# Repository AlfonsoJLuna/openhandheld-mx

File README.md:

# OpenHandheld MX

Open-source development board in the shape of a handheld game console.

 | 
:---: | :---:
Front | Back

## Related repositories

Example code for this board can be found in [openhandheld-mx-sdk](https://github.com/AlfonsoJLuna/openhandheld-mx-sdk).

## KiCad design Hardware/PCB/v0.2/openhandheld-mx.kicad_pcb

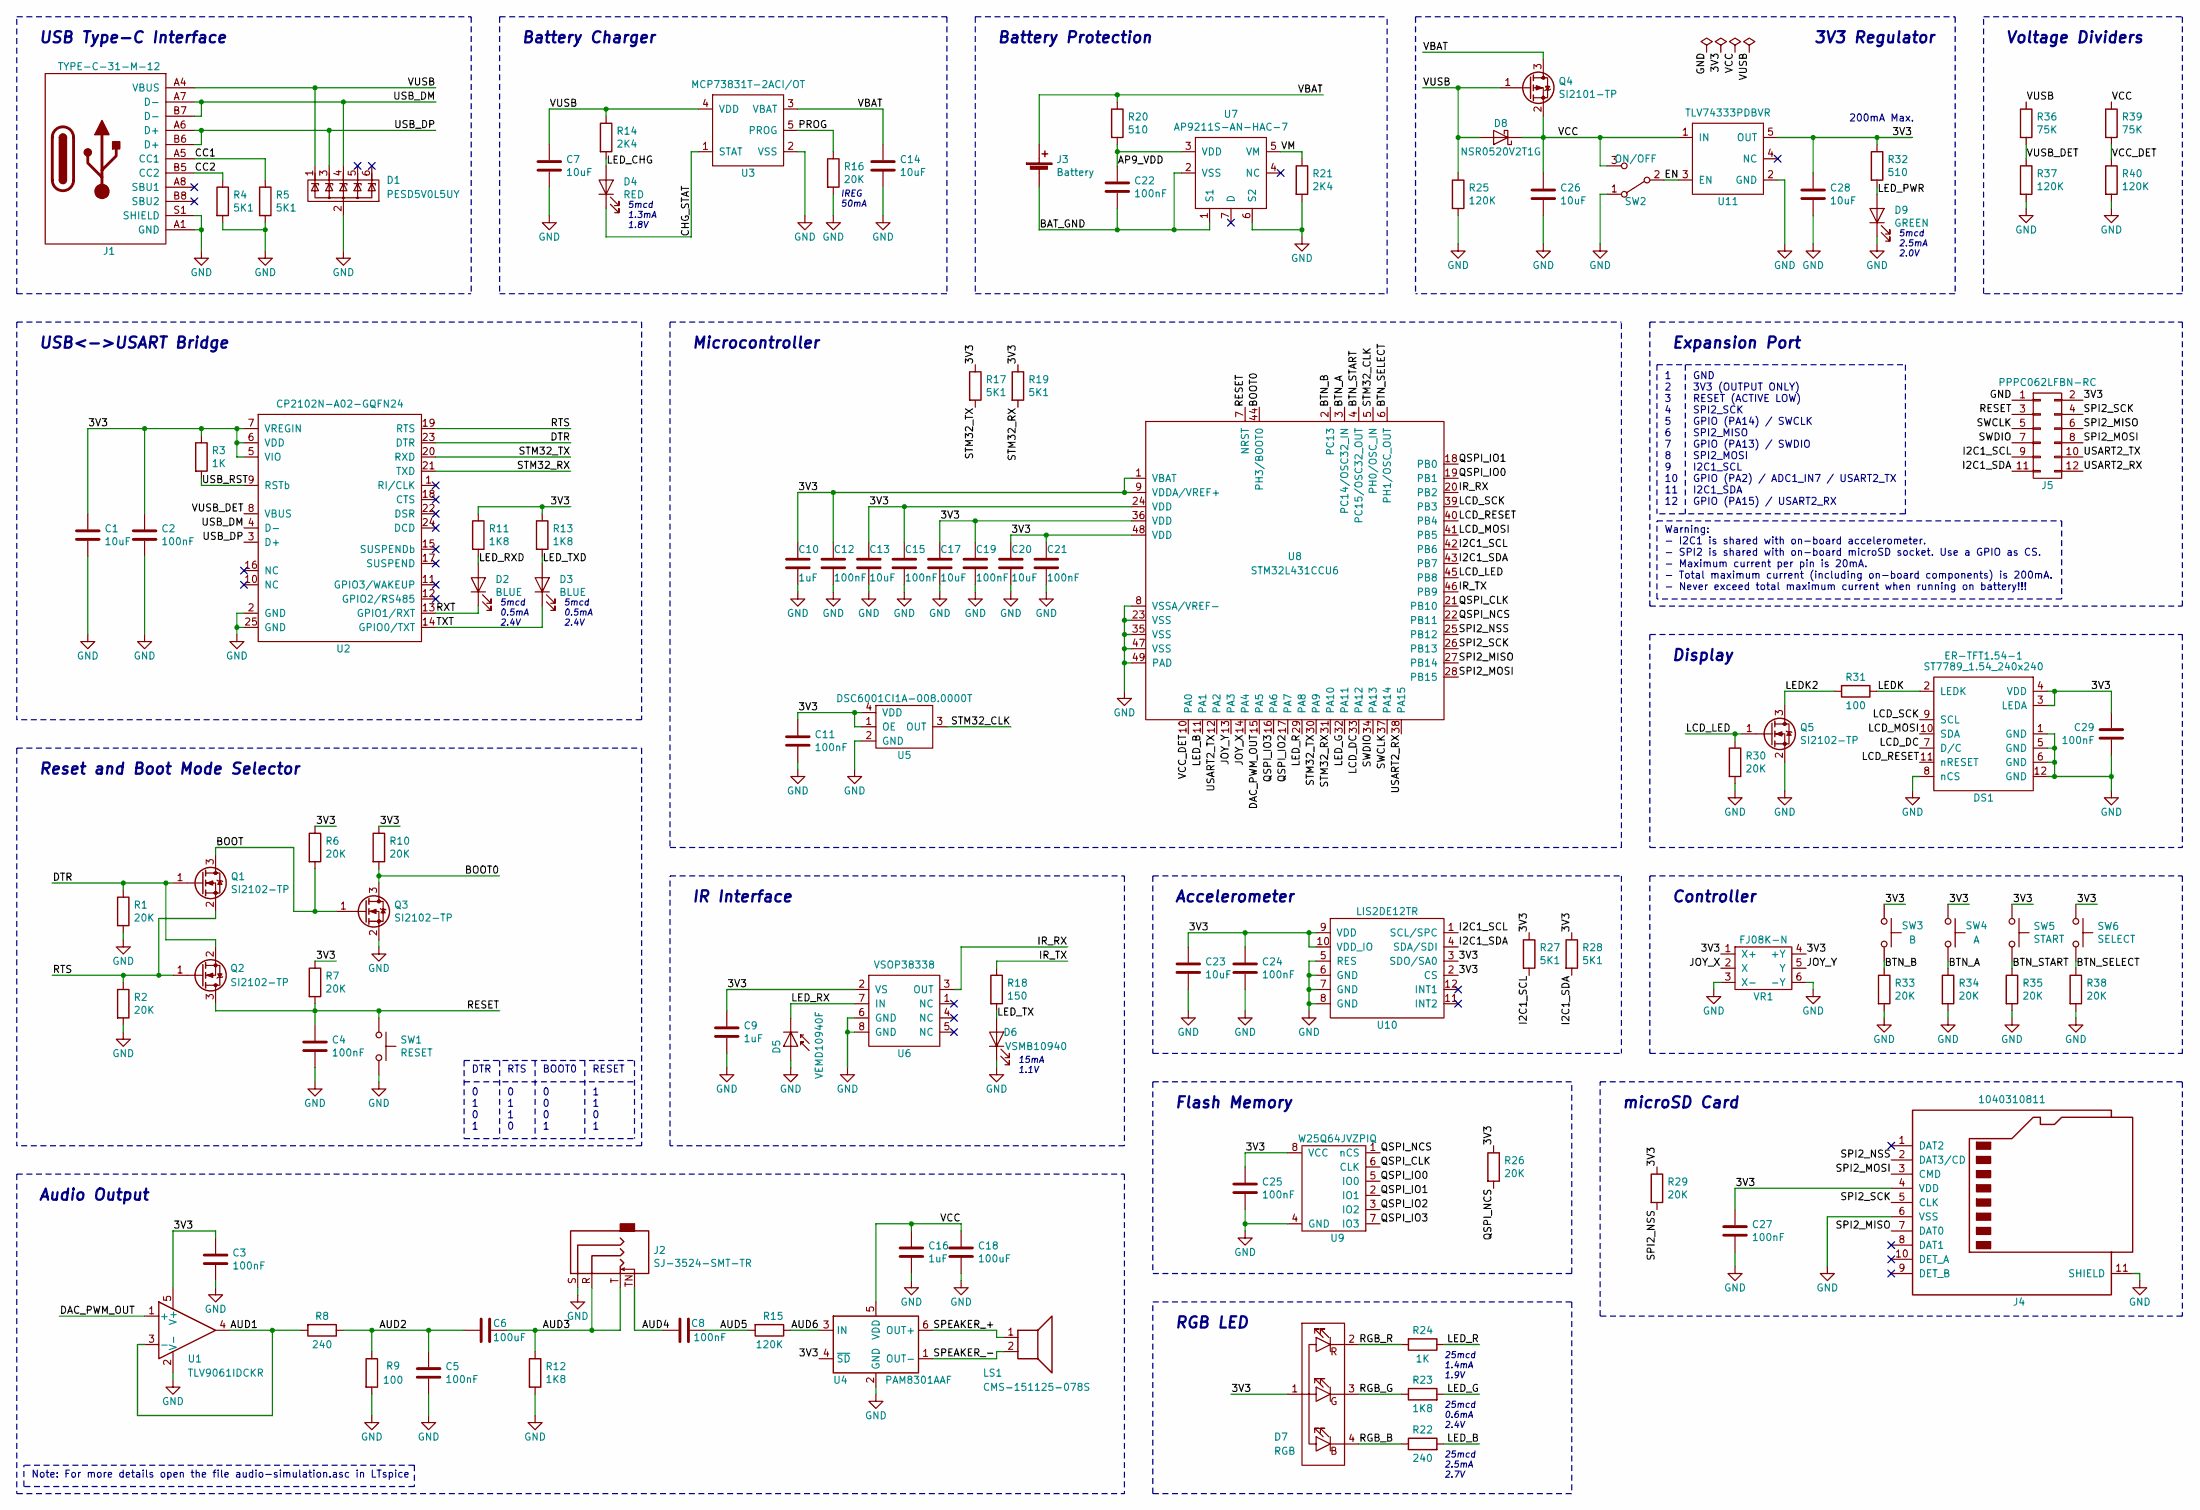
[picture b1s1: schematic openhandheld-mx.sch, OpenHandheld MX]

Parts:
C1, C7, C13, C14, C17, C20, C23, C26, C28: 10uF; C_0603_1608Metric; MPN CL10A106KP8NNNC
C2, C3, C4, C5, C8, C11, C12, C15, C19, C21, C22, C24, C25, C27, C29: 100nF; C_0402_1005Metric; MPN CL05B104KO5NNNC
C6, C18: 100uF; C_1210_3225Metric; MPN CL32A107MQVNNNE
C9, C10, C16: 1uF; C_0402_1005Metric; MPN CL05A105KO5NNNC
D1: PESD5V0L5UY; SOT-363_SC-70-6; MPN PESD5V0L5UY
D2, D3: BLUE; LED_0603_1608Metric; MPN 150060BS75000
D4: RED; LED_0603_1608Metric; MPN 150060SS75000
D5: VEMD10940F; Vishay_IR; MPN VEMD10940F
D6: VSMB10940; Vishay_IR; MPN VSMB10940
D7: RGB; 150044M155260; MPN 150044M155260
D8: NSR0520V2T1G; D_SOD-523; MPN NSR0520V2T1G
D9: GREEN; LED_0603_1608Metric; MPN 150060VS75000
DS1: ST7789_1.54_240x240; MPN ER-TFT1.54-1
J1: TYPE-C-31-M-12; MPN TYPE-C-31-M-12
J2: SJ-3524-SMT-TR; MPN SJ-3524-SMT-TR
J3: Battery; Solder_Pad_D2
J4: 1040310811; MPN 1040310811
J5: PPPC062LFBN-RC; PinSocket_2x06_P2.54mm_Vertical; MPN PPPC062LFBN-RC
LS1: CMS-151125-078S; Speaker_15x11mm; MPN CMS-151125-078S
Q1, Q2, Q3, Q5: SI2102-TP; SOT-323_SC-70; MPN SI2102-TP
Q4: SI2101-TP; SOT-323_SC-70; MPN SI2101-TP
R1, R2, R6, R7, R10, R16, R26, R29, R30, R33, R34, R35, R38: 20K; R_0402_1005Metric; MPN RC0402FR-0720KL
R3, R24: 1K; R_0402_1005Metric; MPN RC0402FR-071KL
R4, R5, R17, R19, R27, R28: 5K1; R_0402_1005Metric; MPN RC0402FR-075K1L
R8, R22: 240; R_0402_1005Metric; MPN RC0402FR-07240RL
R9, R31: 100; R_0402_1005Metric; MPN RC0402FR-07100RL
R11, R12, R13, R23: 1K8; R_0402_1005Metric; MPN RC0402FR-071K8L
R14, R21: 2K4; R_0402_1005Metric; MPN RC0402FR-072K4L
R15, R25, R37, R40: 120K; R_0402_1005Metric; MPN RC0402FR-07120KL
R18: 150; R_0402_1005Metric; MPN RC0402FR-07150RL
R20, R32: 510; R_0402_1005Metric; MPN RC0402FR-07510RL
R36, R39: 75K; R_0402_1005Metric; MPN RC0402FR-0775KL
SW1: RESET; EVQP7; MPN EVQ-P7L01P
SW2: ON/OFF; CUS-12TB; MPN CUS-12TB
SW3: B; TL3301TF160QG; MPN TL3301TF160QG
SW4: A; TL3301TF160QG; MPN TL3301TF160QG
SW5: START; EVQP7; MPN EVQ-P7L01P
SW6: SELECT; EVQP7; MPN EVQ-P7L01P
U1: TLV9061IDCKR; SOT-353_SC-70-5; MPN TLV9061IDCKR
U2: CP2102N-A02-GQFN24; QFN-24-1EP_4x4mm_P0.5mm_EP2.6x2.6mm; MPN CP2102N-A02-GQFN24
U3: MCP73831T-2ACI_OT; SOT-23-5; MPN MCP73831T-2ACI/OT
U4: PAM8301AAF; SOT-23-6; MPN PAM8301AAF
U5: DSC6001CI1A-008.0000T; DSC60XX-3.2x2.5; MPN DSC6001CI1A-008.0000T
U6: VSOP38338; MPN VSOP38338
U7: AP9211S-AN-HAC-7; MPN AP9211S-AN-HAC-7
U8: STM32L431CCU6; STM32-UFQFPN48; MPN STM32L431CCU6
U9: W25Q64JVZPIQ; Winbond_WSON8_6x5mm; MPN W25Q64JVZPIQ
U10: LIS2DE12TR; MPN LIS2DE12TR
U11: TLV74333PDBVR; SOT-23-5; MPN TLV74333PDBVR
VR1: FJ08K-N; MPN FJ08K-N

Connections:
/3V3: C1.1, C2.1, C3.1, C9.1, C10.1, C11.1, C12.1, C13.1, C15.1, C17.1, C19.1, C20.1, C21.1, C23.1, C24.1, C25.1, C27.1, C28.1, C29.1, D7.1 (A), DS1.3 (LEDA), DS1.4 (VDD), J4.4 (VDD), J5.2, R3.1, R6.1, R7.1, R10.1, R11.1, R13.1, R17.1, R19.1, R26.1, R27.1, R28.1, R29.1, R32.1, SW3.2, SW4.2, SW5.1, SW6.1, U1.5 (V+), U2.5 (VIO), U2.6 (VDD), U2.7 (VREGIN), U4.4 (~SD), U5.1 (OE), U5.4 (VDD), U6.2 (VS), U8.1 (VBAT), U8.9 (VDDA/VREF+), U8.24 (VDD), U8.36 (VDD), U8.48 (VDD), U9.8 (VCC), U10.2 (CS), U10.3 (SDO/SA0), U10.9 (VDD), U10.10 (VDD_IO), U11.5 (OUT), VR1.1 (X+), VR1.4 (+Y)
/AP9_VDD: C22.1, R20.2, U7.3 (VDD)
/AUD1: R8.2, U1.3 (-), U1.4
/AUD2: C5.1, C6.2, R8.1, R9.1
/AUD3: C6.1, J2.R, J2.T, R12.1
/AUD4: C8.1, J2.TN
/AUD5: C8.2, R15.2
/AUD6: R15.1, U4.3 (IN)
/BAT_GND: C22.2, J3.2 (-), U7.1 (S1), U7.2 (VSS)
/BOOT: Q1.3 (D), Q3.1 (G), R6.2
/BOOT0: Q3.3 (D), R10.2, U8.44 (PH3/BOOT0)
/BTN_A: R34.1, SW4.1, U8.3 (PC14/OSC32_IN)
/BTN_B: R33.1, SW3.1, U8.2 (PC13)
/BTN_SELECT: R38.1, SW6.2, U8.6 (PH1/OSC_OUT)
/BTN_START: R35.1, SW5.2, U8.4 (PC15/OSC32_OUT)
/CC1: J1.A5 (CC1), R5.1
/CC2: J1.B5 (CC2), R4.1
/CHG_STAT: D4.1 (K), U3.1 (STAT)
/DAC_PWM_OUT: U1.1 (+), U8.15 (PA5)
/DTR: Q1.1 (G), Q2.2 (S), R1.1, U2.23 (DTR)
/EN: SW2.2 (B), U11.3 (EN)
/I2C1_SCL: J5.9, R27.2, U8.42 (PB6), U10.1 (SCL/SPC)
/I2C1_SDA: J5.11, R28.2, U8.43 (PB7), U10.4 (SDA/SDI)
/IR_RX: U6.3 (OUT), U8.20 (PB2)
/IR_TX: R18.1, U8.46 (PB9)
/JOY_X: U8.14 (PA4), VR1.2 (X)
/JOY_Y: U8.13 (PA3), VR1.5 (Y)
/LCD_DC: DS1.7 (D/C), U8.33 (PA12)
/LCD_LED: Q5.1 (G), R30.1, U8.45 (PB8)
/LCD_MOSI: DS1.10 (SDA), U8.41 (PB5)
/LCD_RESET: DS1.11 (nRESET), U8.40 (PB4)
/LCD_SCK: DS1.9 (SCL), U8.39 (PB3)
/LEDK: DS1.2 (LEDK), R31.1
/LEDK2: Q5.3 (D), R31.2
/LED_B: R22.2, U8.11 (PA1)
/LED_CHG: D4.2 (A), R14.2
/LED_G: R23.2, U8.32 (PA11)
/LED_PWR: D9.2 (A), R32.2
/LED_R: R24.1, U8.29 (PA8)
/LED_RX: D5.1 (K), U6.7 (IN)
/LED_RXD: D2.2 (A), R11.2
/LED_TX: D6.2 (A), R18.2
/LED_TXD: D3.2 (A), R13.2
/PROG: R16.1, U3.5 (PROG)
/QSPI_CLK: U8.21 (PB10), U9.6 (CLK)
/QSPI_IO0: U8.19 (PB1), U9.5 (IO0)
/QSPI_IO1: U8.18 (PB0), U9.2 (IO1)
/QSPI_IO2: U8.17 (PA7), U9.3 (IO2)
/QSPI_IO3: U8.16 (PA6), U9.7 (IO3)
/QSPI_NCS: R26.2, U8.22 (PB11), U9.1 (nCS)
/RESET: C4.1, J5.3, Q2.3 (D), R7.2, SW1.1, U8.7 (NRST)
/RGB_B: D7.4 (BK), R22.1
/RGB_G: D7.3 (GK), R23.1
/RGB_R: D7.2 (RK), R24.2
/RTS: Q1.2 (S), Q2.1 (G), R2.1, U2.19 (RTS)
/RXT: D2.1 (K), U2.13 (GPIO1/RXT)
/SPEAKER_+: LS1.1, U4.6 (OUT+)
/SPEAKER_-: LS1.2, U4.1 (OUT-)
/SPI2_MISO: J4.7 (DAT0), J5.6, U8.27 (PB14)
/SPI2_MOSI: J4.3 (CMD), J5.8, U8.28 (PB15)
/SPI2_NSS: J4.2 (DAT3/CD), R29.2, U8.25 (PB12)
/SPI2_SCK: J4.5 (CLK), J5.4, U8.26 (PB13)
/STM32_CLK: U5.3 (OUT), U8.5 (PH0/OSC_IN)
/STM32_RX: R19.2, U2.21 (TXD), U8.31 (PA10)
/STM32_TX: R17.2, U2.20 (RXD), U8.30 (PA9)
/SWCLK: J5.5, U8.37 (PA14)
/SWDIO: J5.7, U8.34 (PA13)
/TXT: D3.1 (K), U2.14 (GPIO0/TXT)
/USART2_RX: J5.12, U8.38 (PA15)
/USART2_TX: J5.10, U8.12 (PA2)
/USB_DM: D1.4 (IO3), J1.A7 (D-), J1.B7 (D-), U2.4 (D-)
/USB_DP: D1.3 (IO2), J1.A6 (D+), J1.B6 (D+), U2.3 (D+)
/USB_RST: R3.2, U2.9 (RSTb)
/VBAT: C14.1, J3.1 (+), Q4.3 (D), R20.1, U3.3 (VBAT)
/VCC: C16.1, C18.1, C26.1, D8.1 (K), Q4.2 (S), R39.1, SW2.3 (C), U4.5 (VDD), U11.1 (IN)
/VCC_DET: R39.2, R40.1, U8.10 (PA0)
/VM: R21.1, U7.5 (VM)
/VUSB: C7.1, D1.1 (IO1), D8.2 (A), J1.A4 (VBUS), J1.A9 (VBUS), J1.B4 (VBUS), J1.B9 (VBUS), Q4.1 (G), R14.1, R25.1, R36.1, U3.4 (VDD)
/VUSB_DET: R36.2, R37.1, U2.8 (VBUS)
GND: C1.2, C2.2, C3.2, C4.2, C5.2, C7.2, C9.2, C10.2, C11.2, C12.2, C13.2, C14.2, C15.2, C16.2, C17.2, C18.2, C19.2, C20.2, C21.2, C23.2, C24.2, C25.2, C26.2, C27.2, C28.2, C29.2, D1.2 (GND), D5.2 (A), D6.1 (K), D9.1 (K), DS1.1 (GND), DS1.5 (GND), DS1.6 (GND), DS1.8 (nCS), DS1.12 (GND), J1.A1 (GND), J1.A12 (GND), J1.B1 (GND), J1.B12 (GND), J1.S1 (SHIELD), J2.S, J4.6 (VSS), J4.11 (SHIELD), J5.1, Q3.2 (S), Q5.2 (S), R1.2, R2.2, R4.2, R5.2, R9.2, R12.2, R16.2, R21.2, R25.2, R30.2, R33.2, R34.2, R35.2, R37.2, R38.2, R40.2, SW1.2, SW2.1 (A), U1.2 (V-), U2.2 (GND), U2.25 (GND), U3.2 (VSS), U4.2 (GND), U5.2 (GND), U6.6 (GND), U6.8 (GND), U7.6 (S2), U8.8 (VSSA/VREF-), U8.23 (VSS), U8.35 (VSS), U8.47 (VSS), U8.49 (PAD), U9.4 (GND), U10.5 (RES), U10.6 (GND), U10.7 (GND), U10.8 (GND), U11.2 (GND), VR1.3 (X-), VR1.6 (-Y)

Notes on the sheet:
Battery Charger
Battery Protection
IREG 50mA
5mcd 2.5mA 2.0V
3V3 Regulator
5mcd 1.3mA 1.8V
Voltage Dividers
200mA Max.
Reset and Boot Mode Selector
5mcd 0.5mA 2.4V
USB<->USART Bridge
USB Type-C Interface
Expansion Port
1 2 3 4 5 6 7 8 9 10 11 12
Warning: - I2C1 is shared with on-board accelerometer. - SPI2 is shared with on-board microSD socket. Use a GPIO as CS. - Maximum current per pin is 20mA. - Total maximum current (including on-board components) is 200mA. - Never exceed total maximum current when running on battery!!!
GND 3V3 (OUTPUT ONLY) RESET (ACTIVE LOW) SPI2_SCK GPIO (PA14) / SWCLK SPI2_MISO GPIO (PA13) / SWDIO SPI2_MOSI I2C1_SCL GPIO (PA2) / ADC1_IN7 / USART2_TX I2C1_SDA GPIO (PA15) / USART2_RX
Display
microSD Card
Controller
Audio Output
Note: For more details open the file audio-simulation.asc in LTspice
IR Interface
15mA 1.1V
Accelerometer
25mcd 2.5mA 2.7V
25mcd 1.4mA 1.9V
25mcd 0.6mA 2.4V
RGB LED
Flash Memory
Microcontroller
DTR 0 1 0 1
RESET 1 1 0 1
BOOT0 0 0 0 1
RTS 0 1 1 0

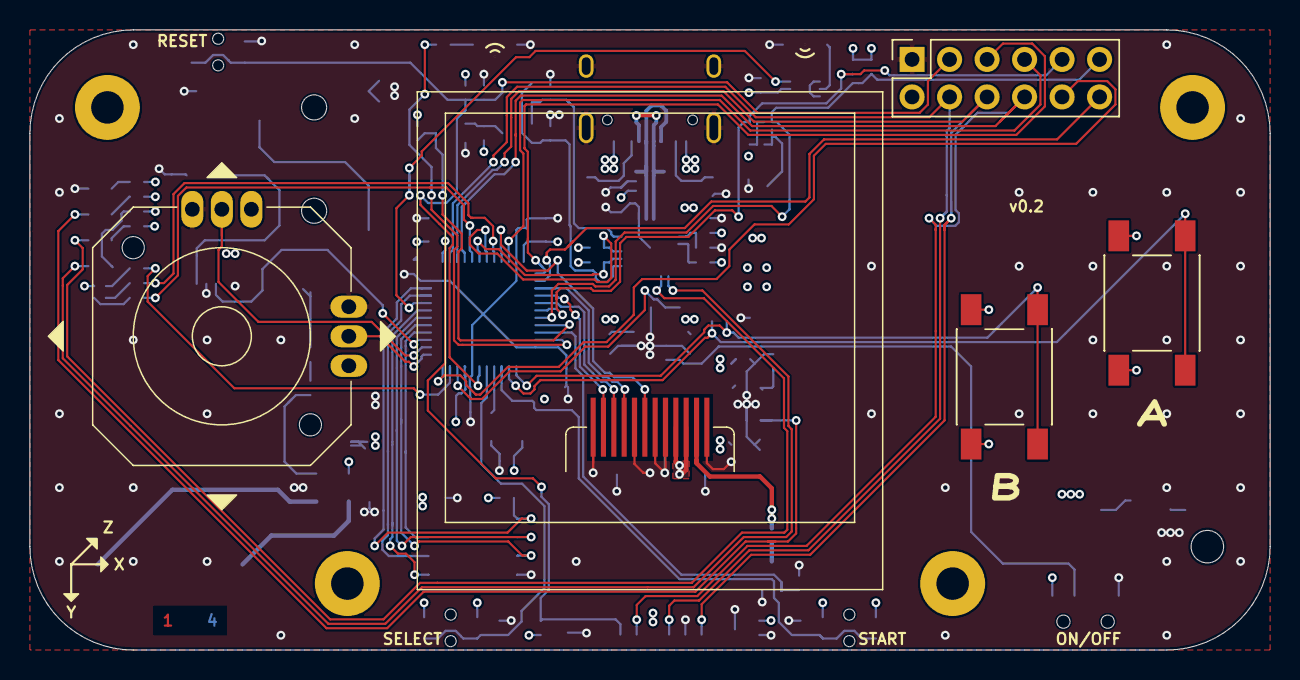
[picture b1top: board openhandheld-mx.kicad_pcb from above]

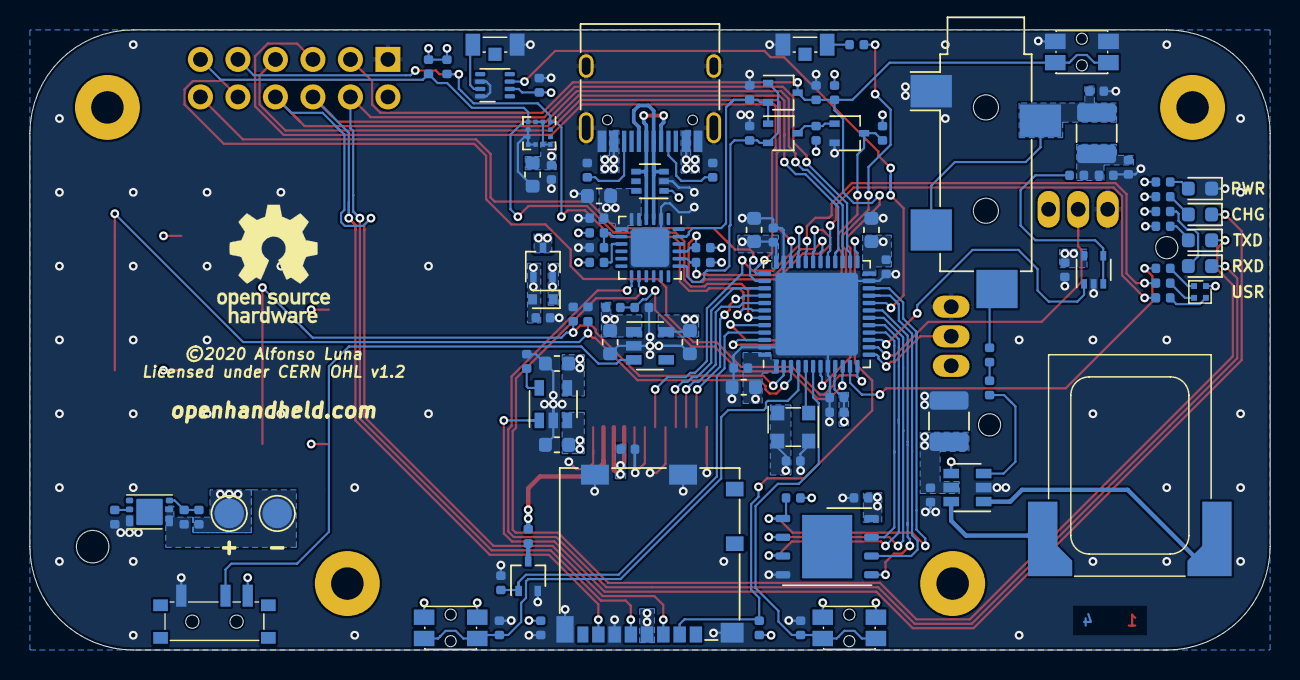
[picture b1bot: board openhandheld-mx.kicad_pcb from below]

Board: 4 copper layers, 84.0 x 42.0 mm, 108 parts (103 on the bottom side), 80 nets.

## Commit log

2020-03-25 Added licenses
2020-03-25 Added v0.1
2020-03-26 Case v0.2: Improved dimensions
2020-04-26 PCB v0.2: Completed schematic
2020-06-17 PCB v0.2: Reduced component dimensions. Preliminary placement
2020-06-21 PCB v0.2: Starting to route
2020-06-28 PCB v0.2: Finished placement, created power planes
2020-07-11 PCB v0.2: Power planes
2020-07-18 PCB v0.2: STM32 fanout
2020-07-18 PCB v0.2: Finished placement. Routing...
2020-07-19 PCB v0.2: Finished routing.
2020-07-20 PCB v0.2: Silkscreen.
2020-08-14 Case v0.2: Finished
2020-08-15 PCB v0.2: Added pdf schematic and pcb renders
2026-04-26 Removed v0.1 files as now there is a dedicated tag
2026-04-26 Deleted firmware folder as now it lives in a different repo
2026-04-26 Added SVG case files
2026-04-26 Updated license
2026-04-26 Added images and updated readme

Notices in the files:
Hardware/PCB/v0.2/openhandheld-mx.kicad_pcb:
©2020 Alfonso Luna
Licensed under CERN OHL v1.2
